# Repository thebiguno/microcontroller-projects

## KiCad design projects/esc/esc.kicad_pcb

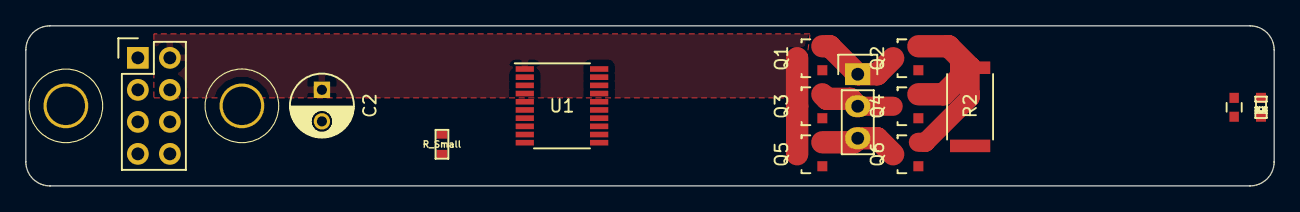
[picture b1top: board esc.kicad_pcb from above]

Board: 2 copper layers, 99.1 x 12.7 mm, 16 parts (0 on the bottom side), 19 nets.

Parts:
C1: C; C_0603
C2: CP1; C_Radial_D5_L6_P2.5
D1: LED; LED-0603
MP1, MP2: MOUNTING_HOLE; MOUNTING_HOLE_#4
P1: INPUT; Pin_Header_Straight_2x04
P2: OUTPUT; Pin_Header_Straight_1x03
Q1, Q3, Q5: Q_PMOS_GSD; SOT-23
Q2, Q4, Q6: Q_NMOS_GSD; SOT-23
R1: R_Small; SM0603_VALUE
R2: RESISTOR; R_2512
U1: CONN_01X20; TSSOP-20_4.4x6.5mm_Pitch0.65mm

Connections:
+BATT: C1.1, C2.1, D1.2, P1.2, Q1.3, Q3.3, Q5.3, U1.1
/CSP: Q2.2, Q4.2, Q6.2, R2.1, U1.11
/FAULT: P1.4, U1.2, U1.4
/GHA: Q1.1, U1.17
/GHB: Q3.1, U1.16
/GHC: Q5.1, U1.15
/GLA: Q2.1, U1.14
/GLB: Q4.1, U1.13
/GLC: Q6.1, U1.12
/SA: P2.1, Q1.2, Q2.3, U1.20
/SB: P2.2, Q3.2, Q4.3, U1.19
/SC: P2.3, Q5.2, Q6.3, U1.18
/SCK: P1.3, U1.6
/SDI: P1.7, U1.8
/SDO: P1.1, U1.5
/SPD: P1.6, U1.3
/STR: P1.5, U1.7
GND: C1.2, C2.2, MP1.1, MP2.1, P1.8, R1.1, R2.2, U1.9, U1.10
unnamed: D1.1, R1.2

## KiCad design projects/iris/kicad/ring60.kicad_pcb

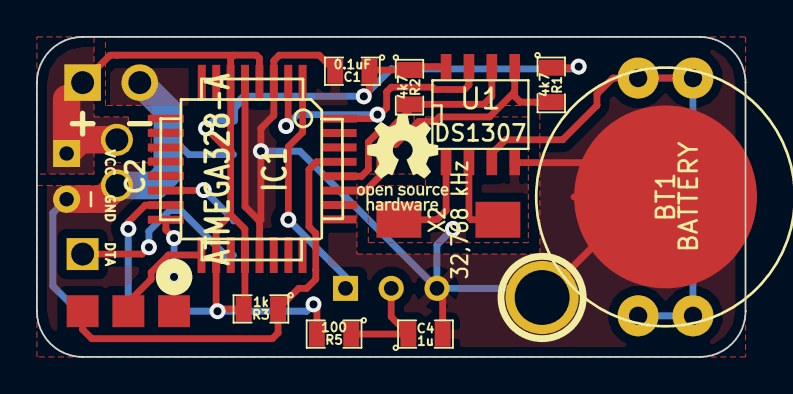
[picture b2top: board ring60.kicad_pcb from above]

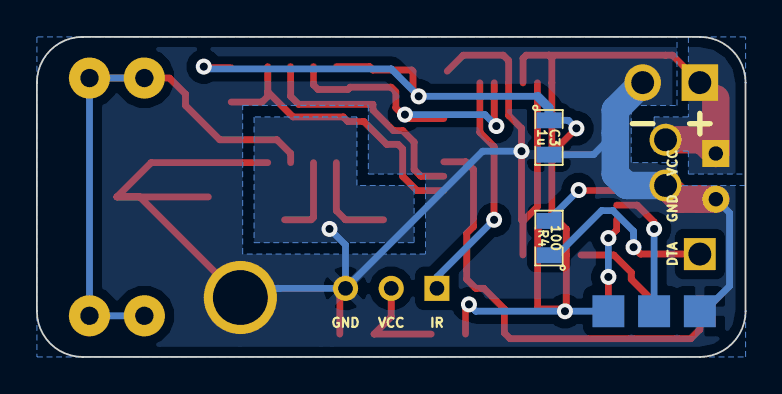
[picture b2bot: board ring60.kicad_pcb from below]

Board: 2 copper layers, 39.4 x 17.8 mm, 20 parts (3 on the bottom side), 16 nets.

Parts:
1PIN: P***; 1pin
BT1: BATTERY; BAT-HLD-012-THM
C1: 0.1uF; SM0805
C2: 100u; cnp_3mm_disc
C3, C4: 1u; SM0805
GND1: CONN_1; SIL-1
IC1: ATMEGA328-A; TQFP32
K1: CONN_3; SIL-3
P1: ISP; ISP_EDGE
R1, R2: 4k7; SM0805
R3: 1k; SM0805
R4, R5: 100; SM0805
U1: DS1307; SO8E
U2: TSOP39338; SIL-3
VAL: REF; Open_Source_Hardware_Logo
VCC1: CONN_1; SIL-1
X2: 32,768 kHz; SM1812L

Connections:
/IROUT: IC1.1, U2.1
/LED_OUT: K1.1, R4.1
/MISO: IC1.16, P1.1
/MOSI: IC1.15, P1.4
/RESET: IC1.29, P1.5, R3.1
/RTC_X1: U1.1, X2.1
/RTC_X2: U1.2, X2.2
/SCK: IC1.17, P1.3
/SCL: IC1.28, R2.2, U1.6
/SDA: IC1.27, R1.2, U1.5
/SQW: IC1.2, IC1.32, U1.7
/VBAT: BT1.1, U1.3
GND: 1PIN.1, BT1.2, C1.2, C2.2, C3.2, C4.2, GND1.1, IC1.3, IC1.5, IC1.21, K1.2, P1.6, U1.4, U2.3
unnamed: C4.1, R5.1, U2.2
unnamed: IC1.14, R4.2
VCC: C1.1, C2.1, C3.1, IC1.4, IC1.6, IC1.18, IC1.20, K1.3, P1.2, R1.1, R2.1, R3.2, R5.2, U1.8, VCC1.1

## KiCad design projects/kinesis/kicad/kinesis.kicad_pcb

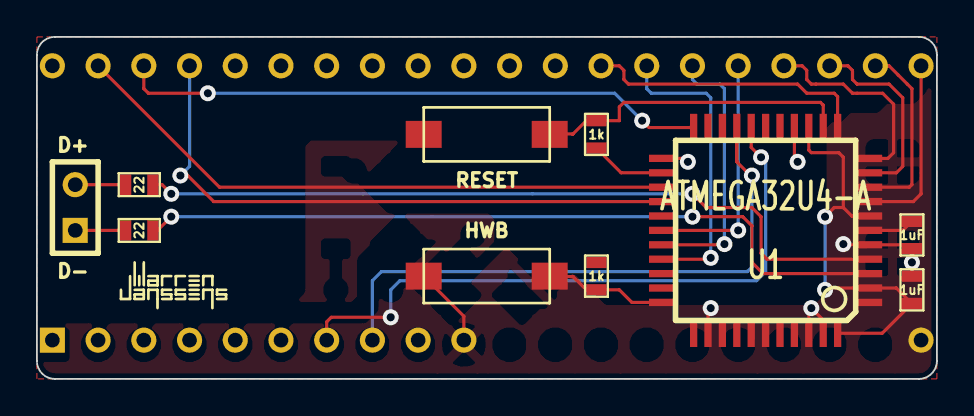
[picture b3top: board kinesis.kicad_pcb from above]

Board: 2 copper layers, 50.0 x 19.0 mm, 12 parts (0 on the bottom side), 30 nets.

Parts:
C4, C5: 1uF; SM0603_VALUE
IC2: AT90S8515-P; DIP-40__600
P1: CONN_2; SIL-2
R2, R3: 22; SM0603_VALUE
R4, R6: 1k; SM0603_VALUE
SW1, SW2: SW_PUSH_SMALL; SW_6x3
U1: ATMEGA32U4-A; TQFP44
WJ10: VAL**; WJ10

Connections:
/A: IC2.39, U1.25
/B: IC2.38, U1.22
/BUZZ: IC2.32, U1.1
/C: IC2.37, U1.26
/D+: R2.2, U1.4
/DL1: IC2.4, U1.38
/DL2: IC2.1, U1.41
/DR1: IC2.2, U1.40
/DR2: IC2.3, U1.39
/G: IC2.36, U1.27
/HWB: R6.1, SW2.1, U1.33
/KP: IC2.5, U1.32
/PGM: IC2.6, U1.31
/R1: IC2.21, U1.8
/R2: IC2.22, U1.9
/R3: IC2.23, U1.10
/R4: IC2.24, U1.11
/R5: IC2.25, U1.28
/R6: IC2.26, U1.29
/R7: IC2.27, U1.30
/R8: IC2.28, U1.12
/RESET: R4.2, SW1.2, U1.13
/SCL: IC2.7, U1.18
/SDA: IC2.8, U1.19
/UCAP: C4.2, U1.6
GND: C4.1, C5.2, IC2.10, IC2.20, SW1.1, SW2.2, U1.5, U1.15, U1.23, U1.35, U1.42, U1.43
unnamed: R3.2, U1.3
unnamed: P1.2, R2.1
unnamed: P1.1, R3.1
VCC: C5.1, IC2.40, R4.1, R6.2, U1.2, U1.7, U1.14, U1.24, U1.34, U1.44

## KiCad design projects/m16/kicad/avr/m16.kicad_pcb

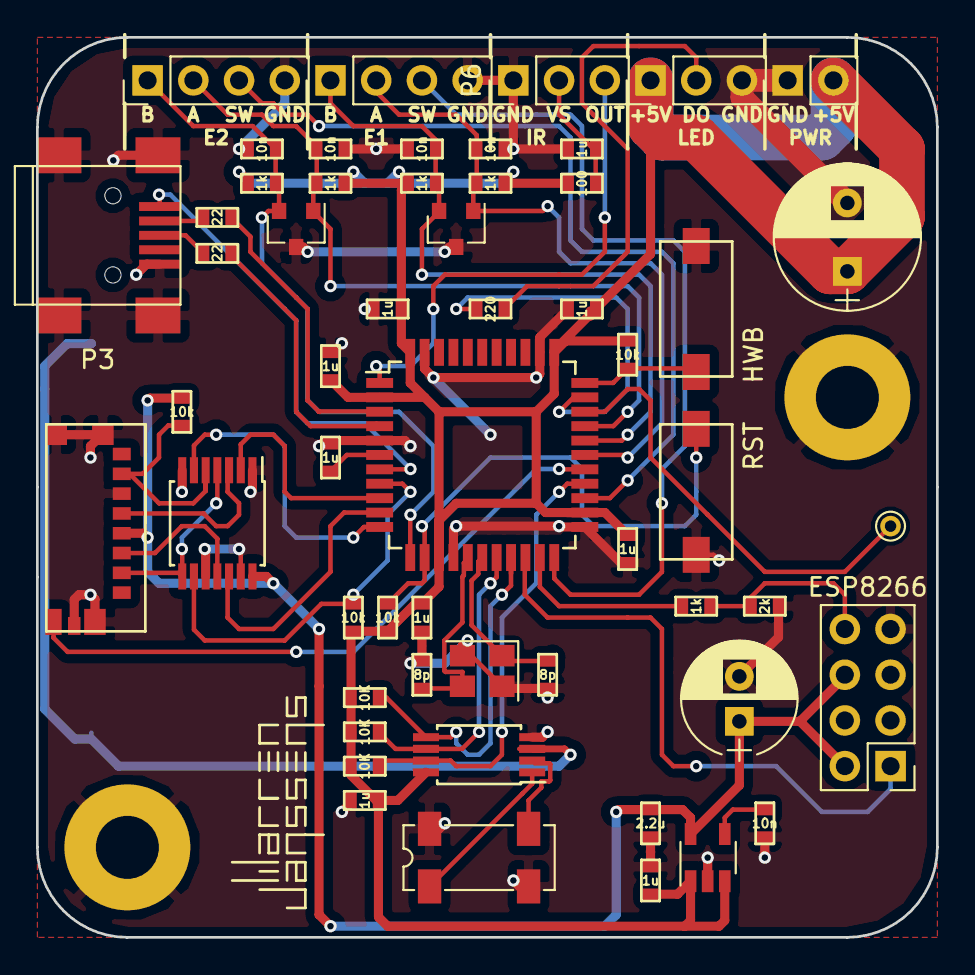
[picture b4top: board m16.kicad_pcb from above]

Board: 2 copper layers, 50.0 x 50.0 mm, 59 parts (1 on the bottom side), 43 nets.

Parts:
BT1: 3V; Keystone_3034_1x20mm-CoinCell
C1, C2, C3, C4, C19: 10n; SM0603_VALUE
C5, C6: 8p; SM0603_VALUE
C7, C8, C9, C10, C11, C12, C13, C15, C18: 1u; SM0603_VALUE
C14: 470u; CP_Radial_D8.0mm_P3.80mm
C16: 100u; CP_Radial_D6.3mm_P2.50mm
C17: 2.2u; SM0603_VALUE
D1, D2: TVS; SOT-23
J2: TEST_1P; PINTST
MP1, MP2: MOUNTING_HOLE; MountingHole_3.5mm_Pad
P1: ENC1; Pin_Header_Straight_1x04_Pitch2.54mm
P2: ENC2; Pin_Header_Straight_1x04_Pitch2.54mm
P3: USB_OTG; USB_Mini-B
P4: Molex 475710001; 475710001
P5: PWR; Pin_Header_Straight_1x02_Pitch2.54mm
P6: IR; Pin_Header_Straight_1x03_Pitch2.54mm
P7: ESP8266; Pin_Header_Straight_2x04_Pitch2.54mm
P8: WS2812; Pin_Header_Straight_1x03_Pitch2.54mm
R1, R2, R3, R4, R14: 1k; SM0603_VALUE
R5, R6, R7, R11: 10k; SM0603_VALUE
R8, R9: 22; SM0603_VALUE
R10, R12, R13: 10K; SM0603_VALUE
R15: 2k; SM0603_VALUE
R16: 220; SM0603_VALUE
R17: 100; SM0603_VALUE
SW1: RST; SW_6x3
SW2: HWB; SW_6x3
U1: 74LS125; TSSOP-14_4.4x5mm_Pitch0.65mm
U2: ATMEGA32U4-A; TQFP-44_10x10mm_Pitch0.8mm
U3: MCP7941X; TSSOP-8_4.4x3mm_Pitch0.65mm
U4: MIC5219-3.3BM5; TSOT-23-5
WJ20: VAL**; WJ20
X1: 16M 8p; Crystal_SMD_3225-4pin_3.2x2.5mm
X2: 32.768k 6-9p; Crystal_SMD_SeikoEpson_MC306-4pin_8.0x3.2mm

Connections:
+3V3: C16.1, C17.1, P4.4, P7.2, P7.6, R5.1, U1.14, U4.5
+5V: C8.1, C9.1, C10.1, C11.1, C12.1, C13.1, C14.1, C15.1, P5.2, P8.1, R1.2, R2.2, R3.2, R4.2, R6.1, R7.1, R10.1, R11.2, R12.1, R13.1, R17.2, U2.2, U2.14, U2.24, U2.34, U2.44, U3.8, U4.1, U4.3
+BATT: BT1.1, U3.3
/CLK: P4.5, U1.3
/CS: P4.2, U1.4, U1.8
/D+: R8.2, U2.4
/D-: R9.2, U2.3
/DET: P4.13, U2.27
/DI: P4.3, U1.11
/DN: P3.2, R9.1
/DO: P4.7, R5.2, U1.5
/DP: P3.3, R8.1
/E1A: C1.2, D1.1, P1.2, R1.1, U2.28
/E1B: C3.2, D1.2, P1.1, R3.1, U2.29
/E1S: P1.3, U2.22
/E2A: C2.2, D2.1, P2.2, R2.1, U2.30
/E2B: C4.2, D2.2, P2.1, R4.1, U2.12
/E2S: P2.3, U2.25
/HWB: R11.1, SW2.1, U2.33
/IROUT: P6.3, U2.1
/LED: R16.2, U2.32
/MFP: R13.2, U2.26, U3.7
/MISO: U1.6, U2.11
/MOSI: U1.12, U2.10
/RST: R7.2, SW1.2, U2.13
/RX_TX: P7.1, U2.20
/SCL: R10.2, U2.18, U3.6
/SCLK: U1.2, U2.9
/SDA: R12.2, U2.19, U3.5
/SS: R6.2, U1.9, U2.8
/TX_RX: R14.2, U2.21
/VBUS: P3.1, U2.7
/X+: C5.2, U2.17, X1.1
/X-: C6.2, U2.16, X1.3
/Y+: U3.1, X2.1
/Y-: U3.2, X2.3
GND: BT1.2, C1.1, C2.1, C3.1, C4.1, C5.1, C6.1, C7.1, C8.2, C9.2, C10.2, C11.2, C12.2, C13.2, C14.2, C15.2, C16.2, C17.2, C18.1, C19.2, D1.3, D2.3, MP1.1, MP2.1, P1.4, P2.4, P3.5, P3.6, P4.6, P4.9, P4.10, P4.11, P4.12, P5.1, P6.1, P7.7, P8.3, R15.1, SW1.1, SW2.2, U1.1, U1.7, U1.10, U1.13, U2.5, U2.15, U2.23, U2.35, U2.43, U3.4, U4.2, X1.2, X1.4, X2.2, X2.4
unnamed: C7.2, U2.6
unnamed: C18.2, P6.2, R17.1
unnamed: C19.1, U4.4
unnamed: J2.1, U2.31
unnamed: P7.8, R14.1, R15.2
unnamed: P8.2, R16.1

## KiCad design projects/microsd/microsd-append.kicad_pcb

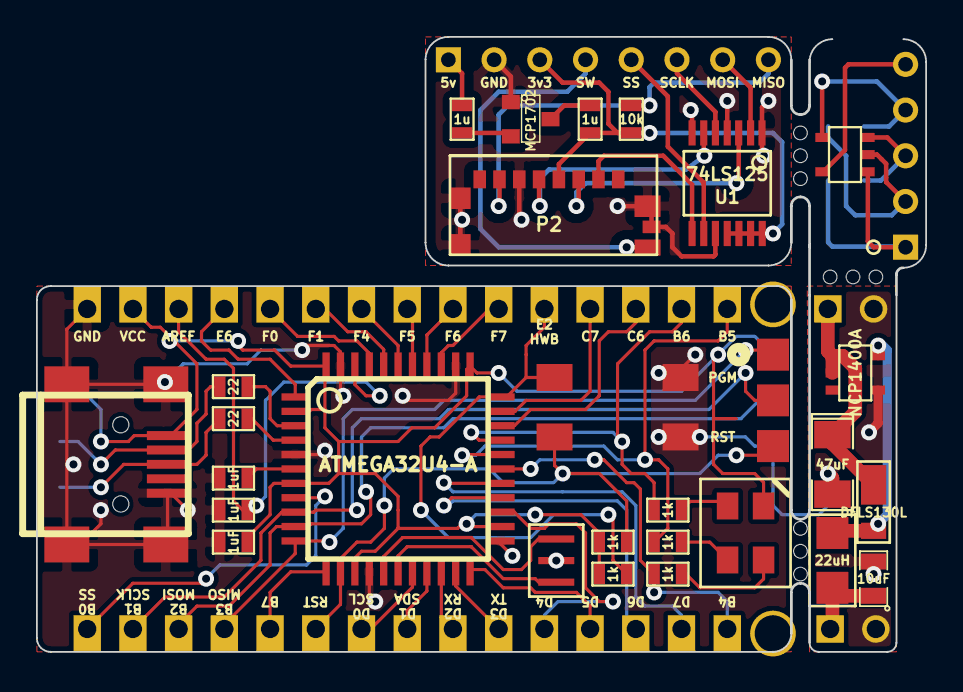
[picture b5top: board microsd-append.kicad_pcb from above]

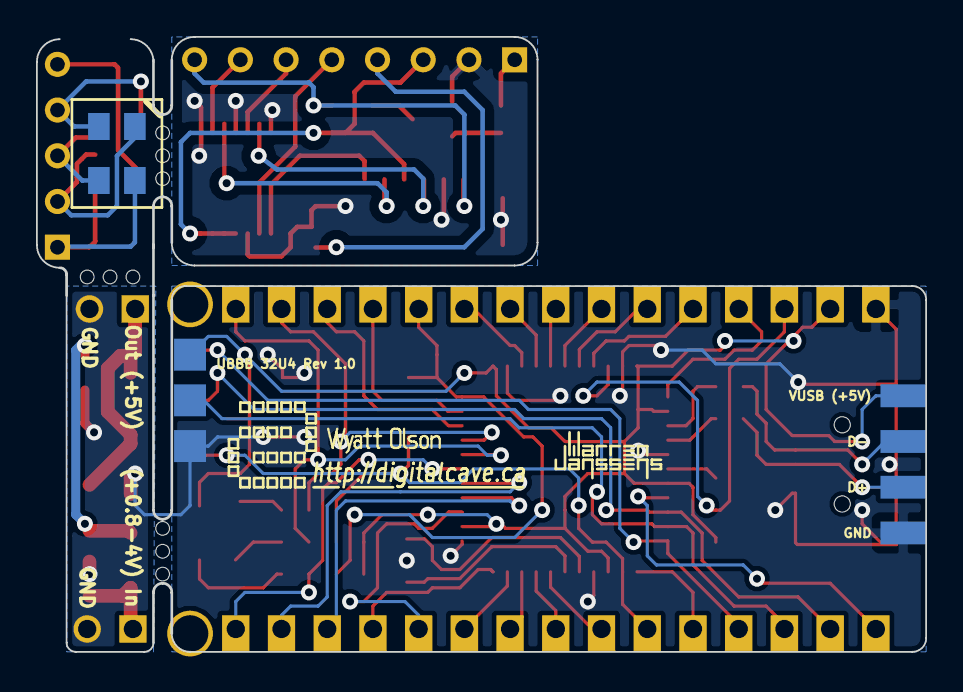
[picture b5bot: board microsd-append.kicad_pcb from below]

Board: 2 copper layers, 49.4 x 34.2 mm, 50 parts (6 on the bottom side), 57 nets.

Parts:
1PIN, 1PIN#2: P***; 1pin
C1: 10uF; SM0805
C1#2, C2#2: 1u; SM0603_VALUE
C2: 47uF; SM1206POL
C3, C4, C5: 1uF; SM0603_VALUE
CON1: USB-MINI-B; USB_MINI_B_fixed
D1: DFLS130L; POWERDI_123
D1#2: RGB_LED_COMMON_ANODE_ALT1; LED_RGB_4-PLCC_ALT1
D2: RGB_LED_COMMON_ANODE; LED_RGB_4-PLCC_ALT1
DIGITALCAVE_URL: VAL**; DIGITALCAVE_URL
L1: 22uH; SM1007
P1: ISP; ISP_EDGE
P1#2, P2#2: CONN_2; PIN_ARRAY_2X1
P1#3: CONN_5; SIL-5
P1#4: CONN_8; SIL-8
P2, P3, P4, P5, P6, P7: CONN_5; PIN_ARRAY_5x1
P2#3: CONN_13; 475710001
PIN_ARRAY_4X1: Val**; PIN_ARRAY_4x1
R1: 10k; SM0603_VALUE
R2, R3: 22; SM0603_VALUE
R4, R5, R6, R7, R8: 1k; SM0603_VALUE
SW1, SW2: SW_PUSH_SMALL; SW_6x3
U1: ATMEGA32U4-A; TQFP44
U1#2: 74LS125; SSOP-14
VAL: REF; DIGITALCAVE_LOGO
VAL#2: DIGITALCAVE_AUTHOR
VR1, VR1#2: NCP1400A; SOT23-5
VR1#3: MCP1702; SOT23
WJ10: VAL**; WJ10
X1: RESONATOR; RESONATOR_SMD-3
mouse_bites: VAL**; mouse_bites
mouse_bites#2, mouse_bites#3: VAL**; mouse_bites

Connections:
+5V: C5.1, CON1.1, D2.2, P1.2, P2.2, PIN_ARRAY_4X1.4, R4.1, R6.2, U1.2, U1.7, U1.14, U1.24, U1.34, U1.44
/5V: C2#2.2, P1#4.1
/AREF: C3.2, P2.3, U1.42
/B0: P7.5, U1.8
/B1: P1.3, P7.4, U1.9
/B2: P1.4, P7.3, U1.10
/B3: P1.1, P7.2, U1.11
/B4: P5.1, R5.2, U1.28
/B5: P4.5, R7.2, U1.29
/B6: P4.4, R8.2, U1.30
/B7: P7.1, U1.12
/C6: P4.3, U1.31
/C7: P4.2, U1.32
/CLK: P2#3.5, U1#2.6
/CS: P2#3.2, U1#2.8
/D0: P6.4, U1.18
/D1: P6.3, U1.19
/D2: P6.2, U1.20
/D3: P6.1, U1.21
/D4: P5.5, U1.25
/D5: P5.4, U1.22
/D6: P5.3, U1.26
/D7: P5.2, U1.27
/D+: CON1.3, PIN_ARRAY_4X1.2, R2.1
/D-: CON1.2, PIN_ARRAY_4X1.3, R3.1
/DET: P1#4.4, P2#3.13
/DI: P2#3.3, U1#2.3
/DO: P1#4.8, P2#3.7, R1.1
/E2: P4.1, R6.1, SW2.1, U1.33
/E6: P2.4, U1.1
/F0: P2.5, U1.41
/F1: P3.1, U1.40
/F4: P3.2, U1.39
/F5: P3.3, U1.38
/F6: P3.4, U1.37
/F7: P3.5, U1.36
/MOSI: P1#4.7, U1#2.2
/RESET: P1.5, P6.5, R4.2, SW1.2, U1.13
/SCLK: P1#4.6, U1#2.5
/SS: P1#4.5, U1#2.9
GND: C1.2, C2.2, C3.1, C4.1, C5.2, CON1.5, CON1.6, CON1.7, CON1.8, CON1.9, P1.6, P1#2.2, P1#4.2, P2.1, P2#2.2, P2#3.6, P2#3.9, P2#3.10, P2#3.11, P2#3.12, PIN_ARRAY_4X1.1, SW1.1, SW2.2, U1.5, U1.15, U1.23, U1.35, U1.43, U1#2.1, U1#2.4, U1#2.7, U1#2.10, VR1.4, VR1#3.1, X1.2
unnamed: C2#2.1, D1#2.1, P1#3.1, VR1#2.1, VR1#3.2
unnamed: C1#2.1, D1#2.3, P1#3.3, VR1#2.3, VR1#3.3
unnamed: D1#2.4, P1#3.4, VR1#2.4
unnamed: P1#3.5, VR1#2.5
unnamed: D1.1, D1#2.2, L1.2, P1#3.2, VR1.5, VR1#2.2
unnamed: C2.1, D1.2, P2#2.1, VR1.1, VR1.2
unnamed: C1.1, L1.1, P1#2.1
unnamed: D2.4, R8.1
unnamed: D2.3, R7.1
unnamed: D2.1, R5.1
unnamed: U1.16, X1.3
unnamed: U1.17, X1.1
unnamed: R2.2, U1.4
unnamed: R3.2, U1.3
unnamed: C4.2, U1.6
VCC: C1#2.2, P1#4.3, P2#3.4, R1.2, U1#2.11, U1#2.12, U1#2.13, U1#2.14

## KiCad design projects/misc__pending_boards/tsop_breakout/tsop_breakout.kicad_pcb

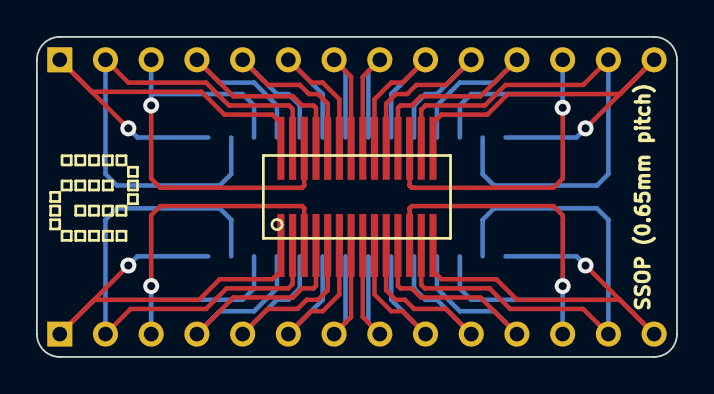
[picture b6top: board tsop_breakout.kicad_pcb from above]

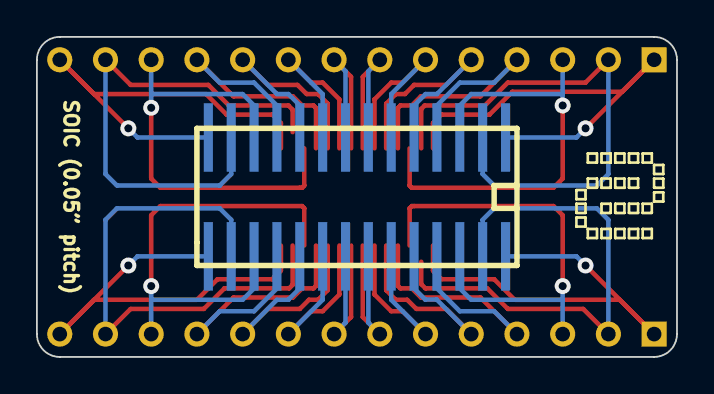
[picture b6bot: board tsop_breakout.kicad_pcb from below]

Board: 2 copper layers, 35.6 x 17.8 mm, 6 parts (2 on the bottom side), 28 nets.

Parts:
K1: PINS_28; ssop-28
K2, K3: PINS_14; SIL-14
K4: PINS_28; SO28
VAL: REF; DIGITALCAVE_LOGO
VAL#2: REF; DIGITALCAVE_LOGO

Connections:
unnamed: K1.26, K3.3, K4.3
unnamed: K1.27, K3.2, K4.2
unnamed: K1.18, K3.11, K4.11
unnamed: K1.28, K3.1, K4.1
unnamed: K1.19, K3.10, K4.10
unnamed: K1.1, K2.1, K4.28
unnamed: K1.2, K2.2, K4.27
unnamed: K1.3, K2.3, K4.26
unnamed: K1.4, K2.4, K4.25
unnamed: K1.5, K2.5, K4.24
unnamed: K1.6, K2.6, K4.23
unnamed: K1.7, K2.7, K4.22
unnamed: K1.8, K2.8, K4.21
unnamed: K1.9, K2.9, K4.20
unnamed: K1.10, K2.10, K4.19
unnamed: K1.20, K3.9, K4.9
unnamed: K1.11, K2.11, K4.18
unnamed: K1.21, K3.8, K4.8
unnamed: K1.12, K2.12, K4.17
unnamed: K1.22, K3.7, K4.7
unnamed: K1.13, K2.13, K4.16
unnamed: K1.23, K3.6, K4.6
unnamed: K1.14, K2.14, K4.15
unnamed: K1.24, K3.5, K4.5
unnamed: K1.25, K3.4, K4.4
unnamed: K1.17, K3.12, K4.12
unnamed: K1.16, K3.13, K4.13
unnamed: K1.15, K3.14, K4.14

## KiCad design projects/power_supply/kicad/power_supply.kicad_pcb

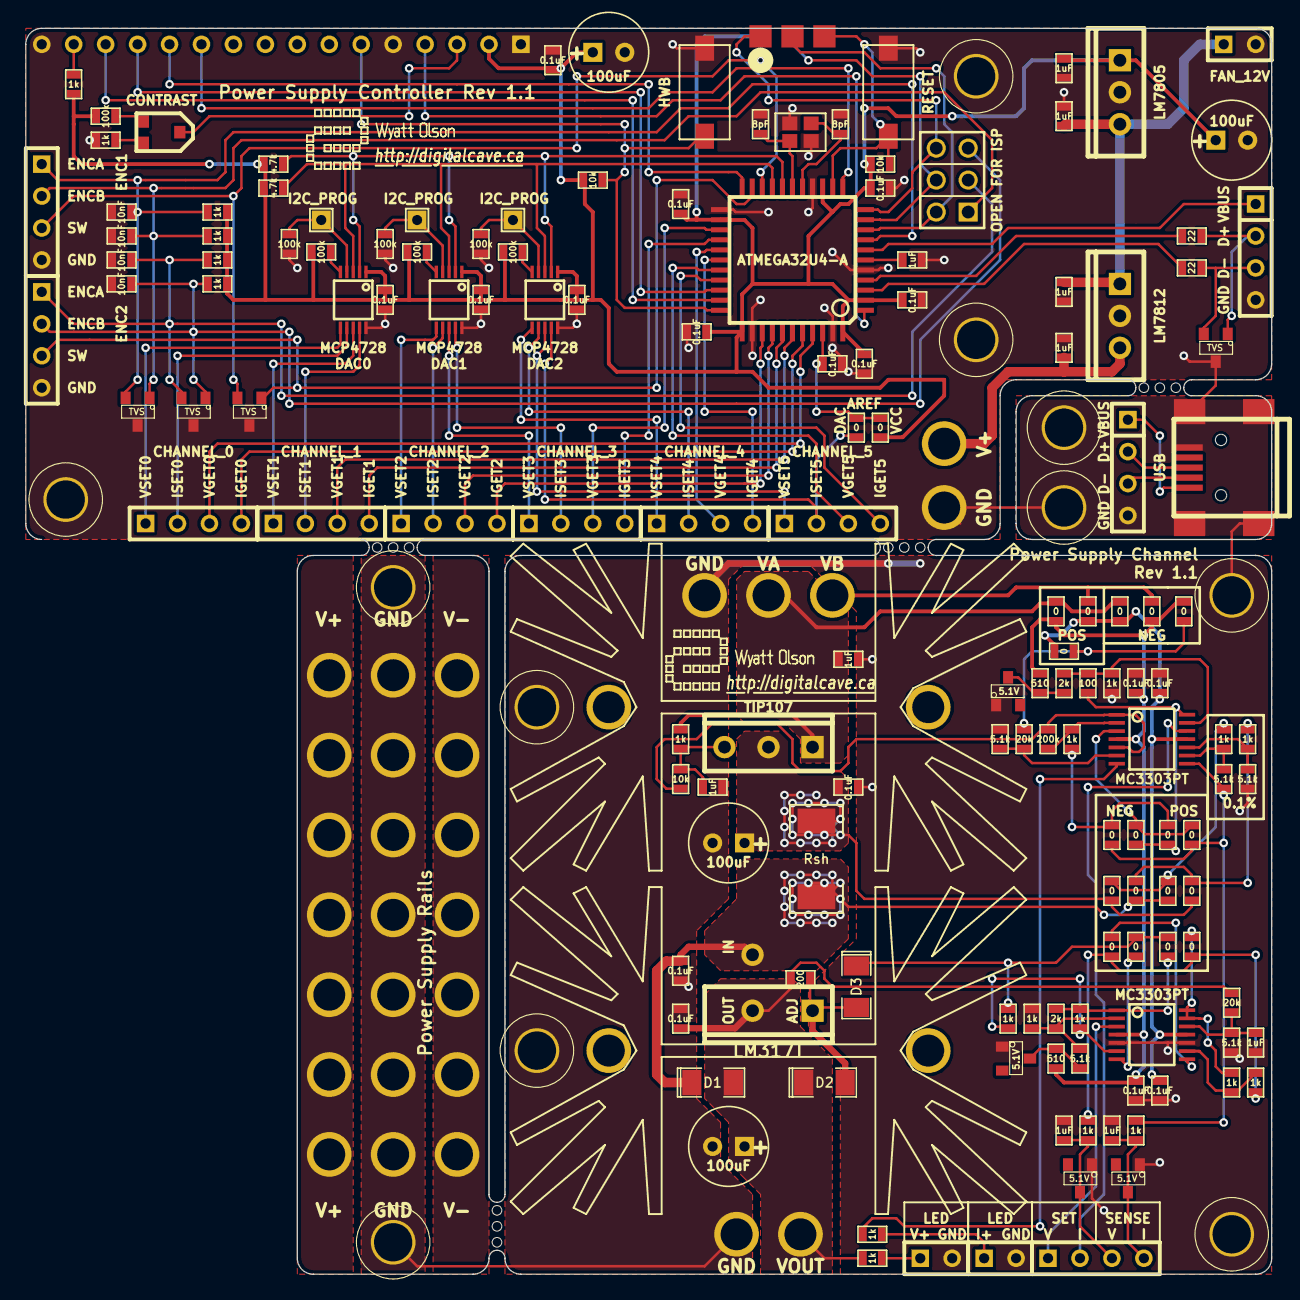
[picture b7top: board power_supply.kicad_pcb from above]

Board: 2 copper layers, 99.1 x 99.1 mm, 185 parts (1 on the bottom side), 111 nets.

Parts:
C1, C2, C3, C4: 100uF; C1V7
C5, C6, C7, C8, C9, C11, C12, C17, C18, C19, C20, C21, C22, C34, C35, C36, C37: 0.1uF; SM0603_VALUE
C10, C13, C14, C15, C16, C24, C25, C31, C32, C33: 1uF; SM0603_VALUE
C23, C26: 8pF; SM0603_VALUE
C27, C28, C29, C30: 10nF; SM0603_VALUE
CON1: USB-MINI-B; USB_MINI_B_fixed
D1, D2, D3: SCHOTTKEY; SM1206_DIODE
D4, D5, D6, D7: 5.1V; SOT23-SPECIAL
D8, D9, D10, D11: TVS; SOT23
DS1: HD44780; SIL-16
K1, K2, K3, K4, K5, K6, K7: VS; SCREW_TERMINAL_3
K8: V_LED; SIL-2
K9: SUPPLY; SCREW_TERMINAL_3
K10: VOUT; SCREW_TERMINAL_2
K11: CONTROL_FEEDBACK; SIL-4
K12, K14: HEATSINK; HEATSINK_OHMITE_FSERIES
K13: I_LIM_LED; SIL-2
K15, K17: USB; SIL-4
K16: POWER; SCREW_TERMINAL_2
K18: ENC1; SIL-4
K19: ENC2; SIL-4
K20: FAN_12V; SIL-2
K21, K22, K23: I2C_PROG; SIL-1
K24: CHANNEL_0; SIL-4
K25: CHANNEL_1; SIL-4
K26: CHANNEL_2; SIL-4
K27: CHANNEL_3; SIL-4
K28: CHANNEL_4; SIL-4
K29: CHANNEL_5; SIL-4
MP1, MP2, MP5, MP7, MP9, MP11, MP14, MP16, MP17, MP19, MP20: MOUNTING_HOLE; MOUNTING_HOLE_#4
MP3, MP4, MP6, MP13: MOUSE_BITES; mouse_bites
MP8, MP15: GRAPHIC; DIGITALCAVE_AUTHOR
MP10, MP18: GRAPHIC; DIGITALCAVE_LOGO
MP12, MP21: GRAPHIC; DIGITALCAVE_URL
P1: ISP; ISP_EDGE
P2: PROG_JMP; pin_array_3x2
Q1: TIP107; TO220_VERT
R1: Rsh; SM2512
R2, R3, R7, R8, R9, R15, R17, R22, R25, R26, R29, R31, R33, R37, R40, R44, R58, R59, R66, R69: 0; SM0603_VALUE
R4, R5, R11, R12, R13, R18, R30, R32, R34, R35, R36, R38, R39, R41, R45, R47, R53, R54, R55, R56: 1k; SM0603_VALUE
R6: 200; SM0603_VALUE
R10, R67: 20k; SM0603_VALUE
R14, R19, R24, R42, R68: 5.1k; SM0603_VALUE
R16, R21: 510; SM0603_VALUE
R20, R28: 2k; SM0603_VALUE
R23: 100; SM0603_VALUE
R27, R48, R57: 10k; SM0603_VALUE
R43: 200k; SM0603_VALUE
R46, R60, R61, R62, R63, R64, R65: 100k; SM0603_VALUE
R49, R52: 22; SM0603_VALUE
R50, R51: 4.7k; SM0603_VALUE
RV1: 10k; POTENTIOMETER_SMD
SW1: RESET; SW_6x3
SW2: HWB; SW_6x3
U1: ATMEGA32U4-A; TQFP44
U2, U3: MC3303PT; TSSOP14
U4: LM317T; TO220_VERT
U5: LM7812; TO220_VERT
U6: LM7805; TO220_VERT
U7, U8, U9: MCP4728; MSOP10-0.5
X1: CRYSTAL_SMD_4PIN; CRYSTAL_SMD_2.5x2

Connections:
+5V: C3.1, C4.1, C17.2, C18.2, C19.2, C20.2, C21.2, C22.2, C33.1, C35.2, C36.2, C37.2, DS1.2, P1.2, R46.1, R47.2, R48.1, R50.2, R51.2, R53.2, R54.2, R55.2, R56.2, R57.2, R58.2, R63.1, R64.1, R65.1, U1.2, U1.14, U1.24, U1.34, U1.44, U6.VO, U7.1, U8.1, U9.1
+12V: C25.1, C32.1, K20.1, U5.VO, U6.VI
/AREF: C34.2, R58.1, R59.1, U1.42
/CONT_PWR_IN: C24.1, K16.2, U5.VI
/D4: DS1.11, U1.12
/D5: DS1.12, U1.22
/D6: DS1.13, U1.31
/D7: DS1.14, U1.32
/E: DS1.6, R57.1, SW2.1, U1.33
/ENC1_A: C28.2, D9.2, K18.1, R54.1, U1.8
/ENC1_B: C27.2, D9.1, K18.2, P2.1, R53.1
/ENC1_SW: D8.2, K18.3, U1.20
/ENC2_A: C30.2, D10.2, K19.1, P2.3, R56.1
/ENC2_B: C29.2, D10.1, K19.2, P2.5, R55.1
/ENC2_SW: D8.1, K19.3, U1.21
/I_DIFF: R19.1, R22.2, R30.1, R31.1, U2.8
/I_GET: C16.1, D7.2, K11.4, R30.2
/I_GET0: K24.4, U1.40
/I_GET1: K25.4, U1.38
/I_GET2: K26.4, U1.36
/I_GET3: K27.4, U1.26
/I_GET4: K28.4, U1.28
/I_GET5: K29.4, U1.30
/I_LIM: C13.1, Q1.B, R5.2, R27.1
/I_LIM_LED: R27.2, R43.2, U2.1, U2.5
/I_SET: K11.2, U2.12
/I_SET0: K24.2, U7.7
/I_SET1: K25.2, U7.9
/I_SET2: K26.2, U8.7
/I_SET3: K27.2, U8.9
/I_SET4: K28.2, U9.7
/I_SET5: K29.2, R59.2, U9.9
/I_SET_BIAS: R23.2, R26.1, R37.2, U2.14
/MISO: P1.1, P2.6, U1.11
/MOSI: P1.4, P2.4, U1.10
/POST_CS: C12.1, D1.2, R1.2, R25.1, R33.2, U4.3
/PRE_CS: C1.1, C11.2, Q1.C, R1.1, R17.1, R40.2
/RAIL_V+: K1.1, K2.1, K3.1, K4.1, K5.1, K6.1, K7.1
/RAIL_V-: K1.3, K2.3, K3.3, K4.3, K5.3, K6.3, K7.3
/RESET: P1.5, R48.2, SW1.2, U1.13
/RS: DS1.4, U1.1
/SCK: P1.3, P2.2, U1.9
/SCL: R51.1, U1.18, U7.2, U8.2, U9.2
/SDA: R50.1, U1.19, U7.3, U8.3, U9.3
/UCAP: C31.2, U1.6
/V+: C5.2, C7.2, R2.2, R3.2, R16.1, R21.1, R66.1, U2.4, U3.4
/V-: C6.2, C8.2, R7.2, R8.2, R69.2, U2.11, U3.11
/VA: C10.1, K9.2, Q1.E, R3.1, R5.1, R8.1
/VADJ: D3.2, R29.1, R39.1, R44.2
/VB: K9.3, R2.1, R7.1
/VBUS: K17.1, U1.7
/V_GET: C15.1, D4.2, K11.3, R13.1
/V_GET0: K24.3, U1.41
/V_GET1: K25.3, U1.39
/V_GET2: K26.3, U1.37
/V_GET3: K27.3, U1.25
/V_GET4: K28.3, U1.27
/V_GET5: K29.3, U1.29
/V_OUT: C2.1, C9.2, D1.1, D2.2, K10.2, R4.2, R6.2, R10.2, U4.2
/V_SET: K11.1, U3.3
/V_SET0: K24.1, U7.6
/V_SET1: K25.1, U7.8
/V_SET2: K26.1, U8.6
/V_SET3: K27.1, U8.8
/V_SET4: K28.1, U9.6
/V_SET5: K29.1, U9.8
GND: C1.2, C2.2, C3.2, C4.2, C5.1, C6.1, C7.1, C8.1, C9.1, C10.2, C11.1, C12.2, C13.2, C14.2, C15.2, C16.2, C17.1, C18.1, C19.1, C20.1, C21.1, C22.1, C23.1, C24.2, C25.2, C26.1, C27.1, C28.1, C29.1, C30.1, C31.1, C32.2, C33.2, C34.1, C35.1, C36.1, C37.1, CON1.5, CON1.6, CON1.7, CON1.8, CON1.9, D4.1, D5.1, D6.1, D7.1, D8.3, D9.3, D10.3, D11.3, DS1.1, DS1.5, DS1.16, K1.2, K2.2, K3.2, K4.2, K5.2, K6.2, K7.2, K8.2, K9.1, K10.1, K13.2, K15.4, K16.1, K17.4, K18.4, K19.4, K20.2, MP1.1, MP2.1, MP5.1, MP7.1, MP9.1, MP11.1, MP14.1, MP16.1, MP17.1, MP19.1, MP20.1, P1.6, R14.1, R35.1, R36.1, R42.1, R45.2, R60.2, R61.2, R62.2, R68.2, SW1.1, SW2.2, U1.5, U1.15, U1.23, U1.35, U1.43, U3.5, U3.10, U5.GND, U6.GND, U7.10, U8.10, U9.10, X1.2, X1.4
unnamed: C26.2, U1.16, X1.3
unnamed: C23.2, U1.17, X1.1
unnamed: R67.2, R68.1, U2.6
unnamed: R52.2, U1.3
unnamed: R49.2, U1.4
unnamed: DS1.15, R47.1
unnamed: R22.1, R26.2, U2.3
unnamed: R28.2, R38.1, R44.1, U3.1
unnamed: R29.2, U3.7
unnamed: R45.1, RV1.1
unnamed: R46.2, RV1.2
unnamed: R15.2, U3.8
unnamed: R9.1, R11.1, R13.2, R15.1
unnamed: R31.2, R32.1, R37.1
unnamed: K13.1, R34.2
unnamed: R34.1, U2.7
unnamed: D6.2, R21.2, R24.2
unnamed: CON1.1, K15.1
unnamed: DS1.3, RV1.3
unnamed: R41.2, R42.2, U2.10
unnamed: R18.1, R19.2, U2.9
unnamed: R17.2, R18.2, R25.2
unnamed: R33.1, R40.1, R41.1
unnamed: R20.1, R23.1, R35.2, U2.13
unnamed: D5.2, R16.2, R20.2
unnamed: R66.2, R67.1, R69.1
unnamed: K8.1, R4.1
unnamed: K23.1, R62.1, U9.4
unnamed: K22.1, R61.1, U8.4
unnamed: K21.1, R60.1, U7.4
unnamed: D11.2, K17.3, R52.1
unnamed: D11.1, K17.2, R49.1
unnamed: CON1.2, K15.3
unnamed: CON1.3, K15.2
unnamed: R24.1, R28.1, R36.2, U3.2
unnamed: R11.2, R12.1, U3.9
unnamed: R9.2, R12.2, U3.13, U3.14
unnamed: D2.1, D3.1, R6.1, U4.1
unnamed: R38.2, R39.2, U3.6
unnamed: C14.1, R10.1, R14.2, U3.12
unnamed: R32.2, R43.1, U2.2
unnamed: R64.2, U8.5
unnamed: R63.2, U7.5
unnamed: R65.2, U9.5
